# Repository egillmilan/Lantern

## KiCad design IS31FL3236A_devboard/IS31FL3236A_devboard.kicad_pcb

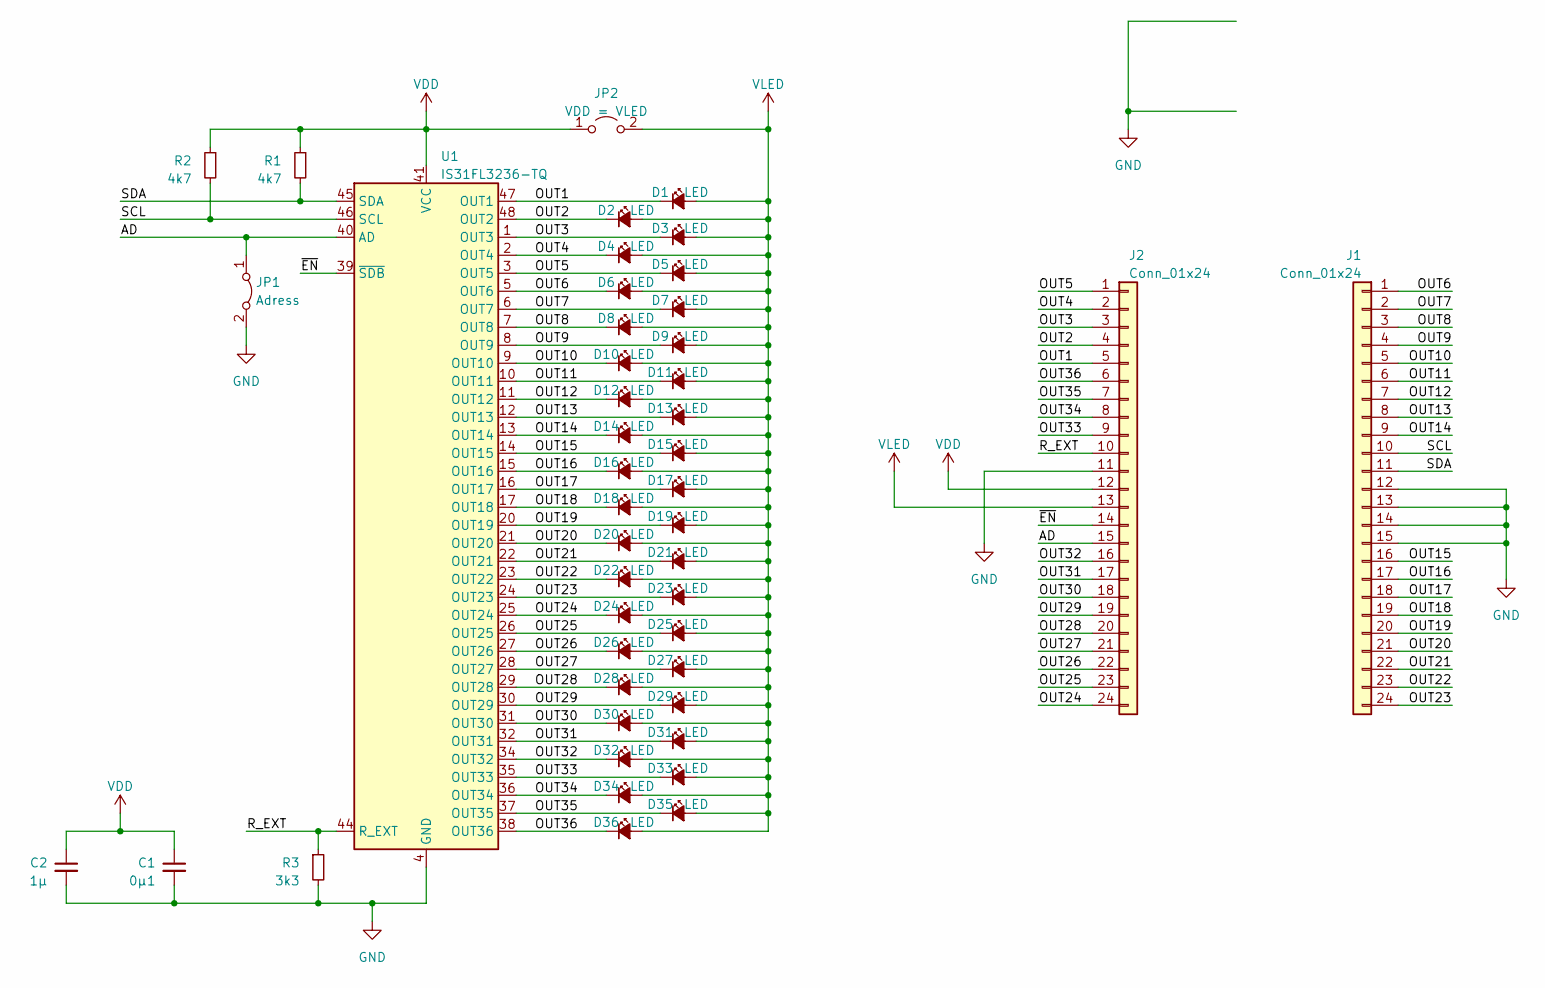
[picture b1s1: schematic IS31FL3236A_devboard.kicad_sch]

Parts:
C1: 0µ1; C_0805_2012Metric_Pad1.18x1.45mm_HandSolder
C2: 1µ; C_0805_2012Metric_Pad1.18x1.45mm_HandSolder
D1, D2, D3, D4, D5, D6, D7, D8, D9, D10, D11, D12, D13, D14, D15, D16, D17, D18, D19, D20, D21, D22, D23, D24, D25, D26, D27, D28, D29, D30, D31, D32, D33, D34, D35, D36: LED; D_1206_3216Metric_Pad1.42x1.75mm_HandSolder
J1, J2: Conn_01x24; PinHeader_1x24_P2.54mm_Vertical
JP1: Adress; SolderJumper-2_P1.3mm_Bridged_RoundedPad1.0x1.5mm
JP2: VDD = VLED; SolderJumper-2_P1.3mm_Open_RoundedPad1.0x1.5mm
R1, R2: 4k7; R_0805_2012Metric_Pad1.20x1.40mm_HandSolder
R3: 3k3; R_0805_2012Metric_Pad1.20x1.40mm_HandSolder
U1: IS31FL3236-TQ; TQFP-48-1EP_7x7mm_P0.5mm_EP4.11x4.11mm

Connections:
/AD: J2.15, JP1.1 (A), U1.40 (AD)
/OUT1: D1.1 (K), J2.5, U1.47 (OUT1)
/OUT2: D2.1 (K), J2.4, U1.48 (OUT2)
/OUT3: D3.1 (K), J2.3, U1.1 (OUT3)
/OUT4: D4.1 (K), J2.2, U1.2 (OUT4)
/OUT5: D5.1 (K), J2.1, U1.3 (OUT5)
/OUT6: D6.1 (K), J1.1, U1.5 (OUT6)
/OUT7: D7.1 (K), J1.2, U1.6 (OUT7)
/OUT8: D8.1 (K), J1.3, U1.7 (OUT8)
/OUT9: D9.1 (K), J1.4, U1.8 (OUT9)
/OUT10: D10.1 (K), J1.5, U1.9 (OUT10)
/OUT11: D11.1 (K), J1.6, U1.10 (OUT11)
/OUT12: D12.1 (K), J1.7, U1.11 (OUT12)
/OUT13: D13.1 (K), J1.8, U1.12 (OUT13)
/OUT14: D14.1 (K), J1.9, U1.13 (OUT14)
/OUT15: D15.1 (K), J1.16, U1.14 (OUT15)
/OUT16: D16.1 (K), J1.17, U1.15 (OUT16)
/OUT17: D17.1 (K), J1.18, U1.16 (OUT17)
/OUT18: D18.1 (K), J1.19, U1.17 (OUT18)
/OUT19: D19.1 (K), J1.20, U1.20 (OUT19)
/OUT20: D20.1 (K), J1.21, U1.21 (OUT20)
/OUT21: D21.1 (K), J1.22, U1.22 (OUT21)
/OUT22: D22.1 (K), J1.23, U1.23 (OUT22)
/OUT23: D23.1 (K), J1.24, U1.24 (OUT23)
/OUT24: D24.1 (K), J2.24, U1.25 (OUT24)
/OUT25: D25.1 (K), J2.23, U1.26 (OUT25)
/OUT26: D26.1 (K), J2.22, U1.27 (OUT26)
/OUT27: D27.1 (K), J2.21, U1.28 (OUT27)
/OUT28: D28.1 (K), J2.20, U1.29 (OUT28)
/OUT29: D29.1 (K), J2.19, U1.30 (OUT29)
/OUT30: D30.1 (K), J2.18, U1.31 (OUT30)
/OUT31: D31.1 (K), J2.17, U1.32 (OUT31)
/OUT32: D32.1 (K), J2.16, U1.34 (OUT32)
/OUT33: D33.1 (K), J2.9, U1.35 (OUT33)
/OUT34: D34.1 (K), J2.8, U1.36 (OUT34)
/OUT35: D35.1 (K), J2.7, U1.37 (OUT35)
/OUT36: D36.1 (K), J2.6, U1.38 (OUT36)
/R_EXT: J2.10, R3.1, U1.44 (R_EXT)
/SCL: J1.10, R2.2, U1.46 (SCL)
/SDA: J1.11, R1.2, U1.45 (SDA)
/~EN: J2.14, U1.39 (~SDB)
GND: C1.2, C2.2, J1.12, J1.13, J1.14, J1.15, J2.11, JP1.2 (B), R3.2, U1.4 (GND), U1.18 (GND), U1.19 (GND), U1.33 (GND), U1.42 (GND), U1.43 (GND), U1.49 (GND)
VDD: C1.1, C2.1, J2.12, JP2.1 (A), R1.1, R2.1, U1.41 (VCC)
VLED: D1.2 (A), D2.2 (A), D3.2 (A), D4.2 (A), D5.2 (A), D6.2 (A), D7.2 (A), D8.2 (A), D9.2 (A), D10.2 (A), D11.2 (A), D12.2 (A), D13.2 (A), D14.2 (A), D15.2 (A), D16.2 (A), D17.2 (A), D18.2 (A), D19.2 (A), D20.2 (A), D21.2 (A), D22.2 (A), D23.2 (A), D24.2 (A), D25.2 (A), D26.2 (A), D27.2 (A), D28.2 (A), D29.2 (A), D30.2 (A), D31.2 (A), D32.2 (A), D33.2 (A), D34.2 (A), D35.2 (A), D36.2 (A), J2.13, JP2.2 (B)

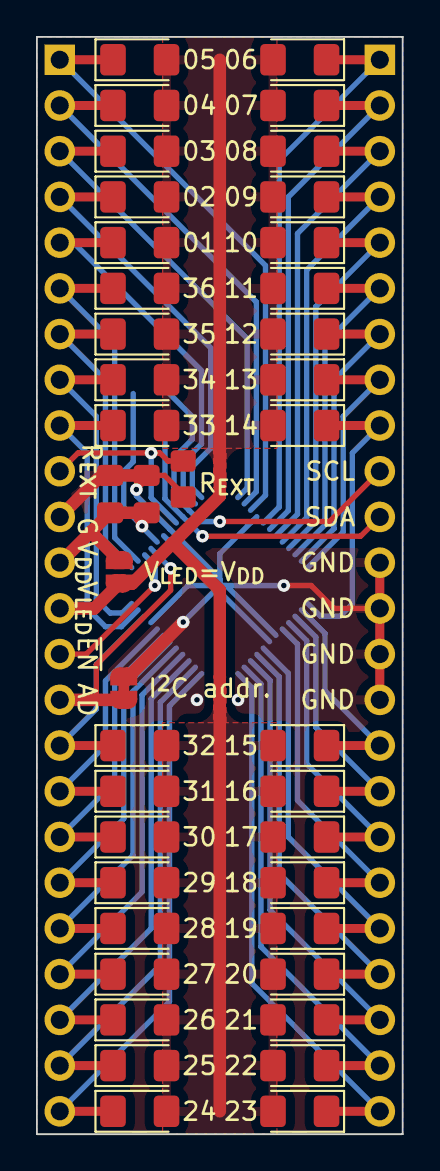
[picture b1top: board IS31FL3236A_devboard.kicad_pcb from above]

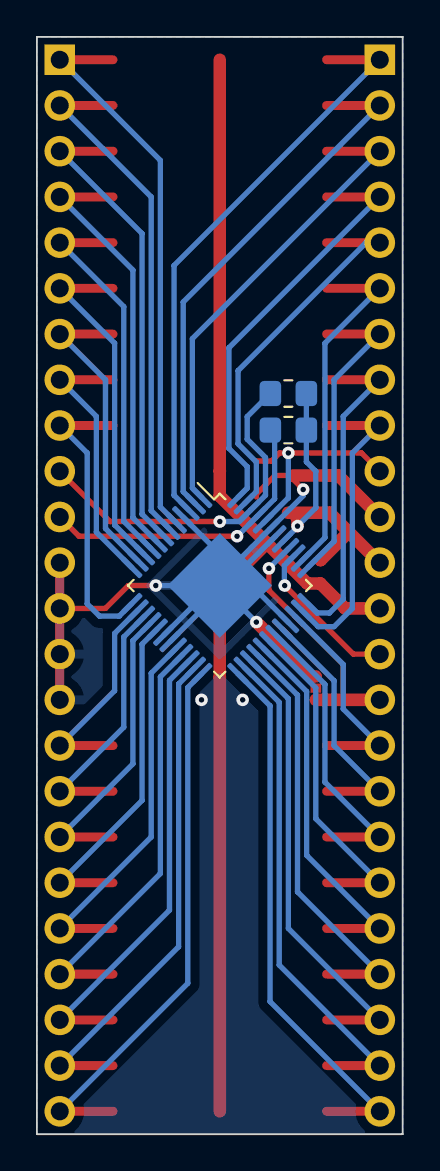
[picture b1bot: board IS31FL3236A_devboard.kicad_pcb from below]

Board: 2 copper layers, 20.3 x 61.0 mm, 46 parts (3 on the bottom side), 44 nets.

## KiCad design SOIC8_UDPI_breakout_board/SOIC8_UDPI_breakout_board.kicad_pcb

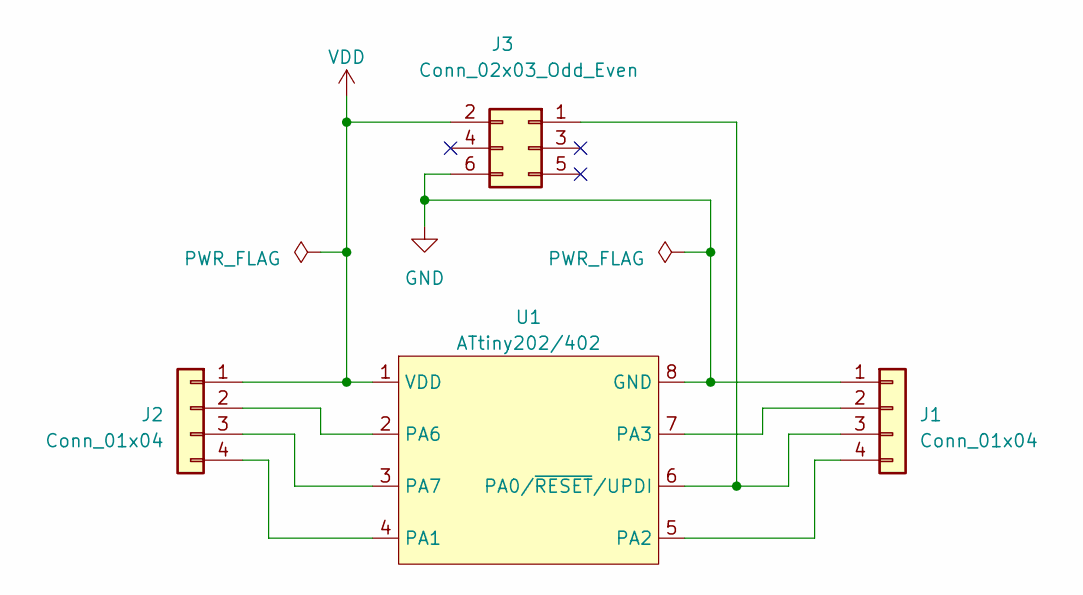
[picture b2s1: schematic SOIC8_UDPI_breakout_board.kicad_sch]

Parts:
J1, J2: Conn_01x04; PinHeader_1x04_P2.54mm_Vertical
J3: Conn_02x03_Odd_Even; PinHeader_2x03_P2.54mm_Vertical
U1: ATtiny202/402; SOIC-8_3.9x4.9mm_P1.27mm

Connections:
GND: J1.1, J3.6, U1.8 (GND)
unnamed: J1.2, U1.7 (PA3)
unnamed: J1.3, J3.1, U1.6 (PA0/~RESET/UPDI)
unnamed: J1.4, U1.5 (PA2)
unnamed: J2.2, U1.2 (PA6)
unnamed: J2.3, U1.3 (PA7)
unnamed: J2.4, U1.4 (PA1)
VDD: J2.1, J3.2, U1.1 (VDD)

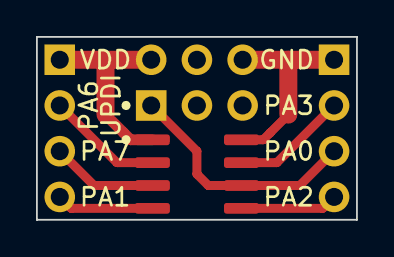
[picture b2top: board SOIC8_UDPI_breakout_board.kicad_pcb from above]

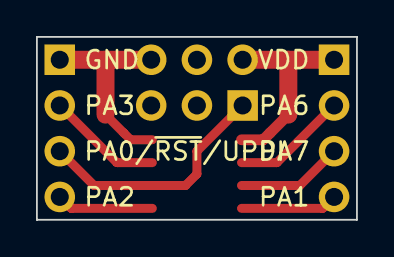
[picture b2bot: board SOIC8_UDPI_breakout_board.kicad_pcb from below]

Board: 2 copper layers, 17.8 x 10.2 mm, 4 parts (2 on the bottom side), 8 nets.

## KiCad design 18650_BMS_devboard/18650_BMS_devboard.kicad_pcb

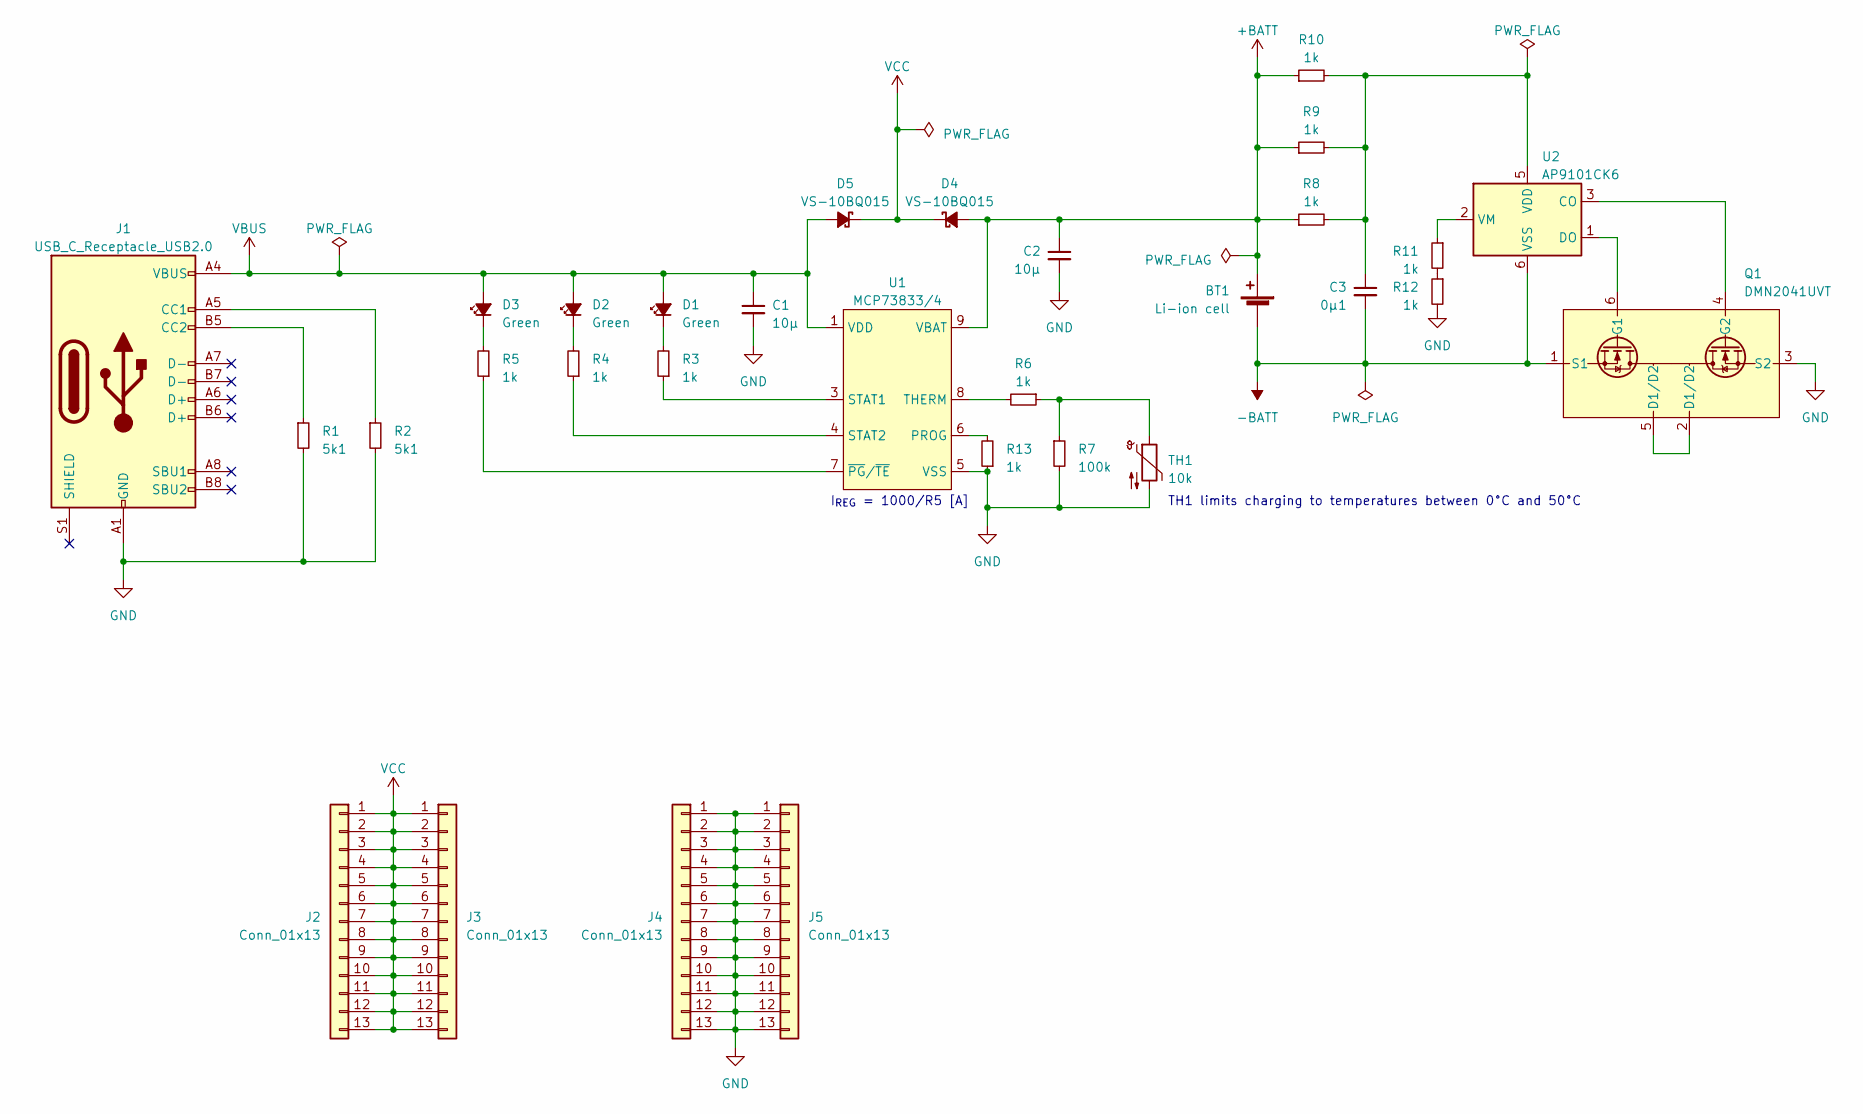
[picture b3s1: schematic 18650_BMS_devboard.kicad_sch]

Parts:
BT1: Li-ion cell; Keystone_254_holder
C1, C2: 10µ; C_0805_2012Metric_Pad1.18x1.45mm_HandSolder
C3: 0µ1; C_0805_2012Metric_Pad1.18x1.45mm_HandSolder
D1, D2, D3: Green; LED_1206_3216Metric_Pad1.42x1.75mm_HandSolder
D4, D5: VS-10BQ015; D_SMB_Handsoldering
J1: USB_C_Receptacle_USB2.0; GCT_USB4120-03-C
J2, J3, J4, J5: Conn_01x13; PinHeader_1x13_P2.54mm_Vertical
Q1: DMN2041UVT; SOT-23-6
R1, R2: 5k1; R_0805_2012Metric_Pad1.20x1.40mm_HandSolder
R3, R4, R5, R6, R8, R9, R10, R11, R12, R13: 1k; R_0805_2012Metric_Pad1.20x1.40mm_HandSolder
R7: 100k; R_0805_2012Metric_Pad1.20x1.40mm_HandSolder
TH1: 10k; R_Axial_DIN0204_L3.6mm_D1.6mm_P1.90mm_Vertical
U1: MCP73833/4; MSOP-10_3x3mm_P0.5mm
U2: AP9101CK6; SOT-23-6

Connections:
+BATT: BT1.1 (+), C2.1, D4.2 (A), R8.1, R9.1, R10.1, U1.9 (VBAT), U1.10 (VBAT)
-BATT: BT1.2 (-), C3.2, Q1.1 (S1), U2.6 (VSS)
GND: C1.2, C2.2, J1.A1 (GND), J1.A12 (GND), J1.B1 (GND), J1.B12 (GND), J4.1, J4.2, J4.3, J4.4, J4.5, J4.6, J4.7, J4.8, J4.9, J4.10, J4.11, J4.12, J4.13, J5.1, J5.2, J5.3, J5.4, J5.5, J5.6, J5.7, J5.8, J5.9, J5.10, J5.11, J5.12, J5.13, Q1.3 (S2), R1.2, R2.2, R7.2, R12.2, R13.1, TH1.2, U1.5 (VSS)
unnamed: D1.1 (K), R3.2
unnamed: D2.1 (K), R4.2
unnamed: D3.1 (K), R5.2
unnamed: J1.A5 (CC1), R2.1
unnamed: J1.B5 (CC2), R1.1
unnamed: Q1.2 (D1/D2), Q1.5 (D1/D2)
unnamed: Q1.6 (G1), U2.1 (DO)
unnamed: Q1.4 (G2), U2.3 (CO)
unnamed: R6.1, R7.1, TH1.1
unnamed: R11.2, R12.1
unnamed: R13.2, U1.6 (PROG)
unnamed: R3.1, U1.3 (STAT1)
unnamed: R4.1, U1.4 (STAT2)
unnamed: R6.2, U1.8 (THERM)
unnamed: R5.1, U1.7 (~PG/~TE)
unnamed: C3.1, R8.2, R9.2, R10.2, U2.5 (VDD)
unnamed: R11.1, U2.2 (VM)
VBUS: C1.1, D1.2 (A), D2.2 (A), D3.2 (A), D5.2 (A), J1.A4 (VBUS), J1.A9 (VBUS), J1.B4 (VBUS), J1.B9 (VBUS), U1.1 (VDD), U1.2 (VDD)
VCC: D4.1 (K), D5.1 (K), J2.1, J2.2, J2.3, J2.4, J2.5, J2.6, J2.7, J2.8, J2.9, J2.10, J2.11, J2.12, J2.13, J3.1, J3.2, J3.3, J3.4, J3.5, J3.6, J3.7, J3.8, J3.9, J3.10, J3.11, J3.12, J3.13

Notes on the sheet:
I_{REG} = 1000/R5 [A]
TH1 limits charging to temperatures between 0°C and 50°C

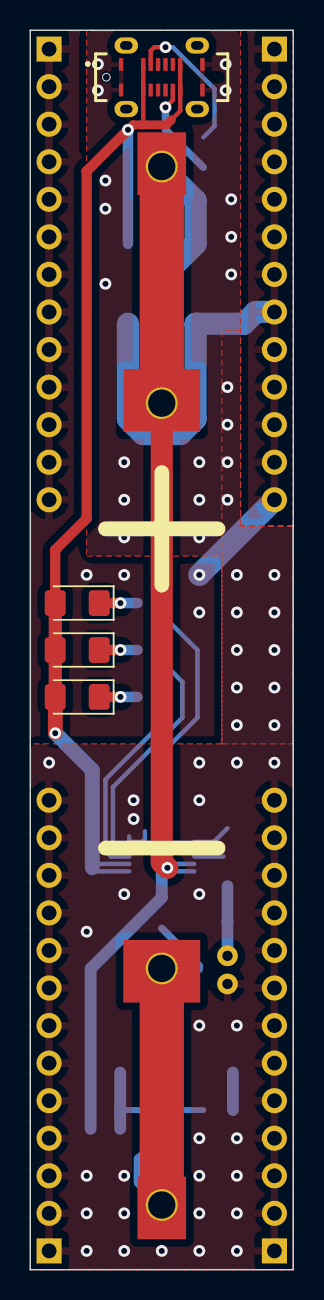
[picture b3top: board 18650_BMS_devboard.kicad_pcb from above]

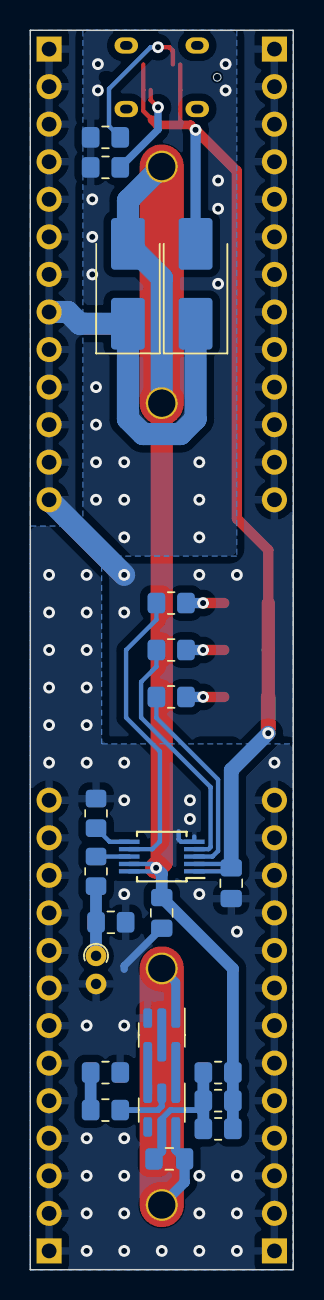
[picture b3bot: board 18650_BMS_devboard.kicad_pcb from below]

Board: 2 copper layers, 17.8 x 83.8 mm, 31 parts (26 on the bottom side), 22 nets.

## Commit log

2023-06-04 LED driver devboeard
